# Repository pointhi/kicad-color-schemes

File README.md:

# kicad-color-schemes

Want to change the color scheme of KiCad? Look here for inspiration.

## Install Color Themes using the PCM (KiCad 5.99 demo feature)

If you run KiCad 5.99 which was build including the new Plugin and Content Manager (using the compile option `-DKICAD_PCM=ON`), you can simply add the repository url and install the themes inside KiCad:
- https://raw.githubusercontent.com/pointhi/kicad-color-schemes/master/repository.json

## How to use a colour theme.

Every theme directory contains the colour definition parts of the eeschema and pcbnew setup files found in your personal profile.
- For Linux under ~.config/kicad/
- Windows XP: “C:\Documents and Settings\username\Application Data” + kicad (= %APPDATA%\kicad)
- Windows Vista & later: “C:\Users\username\AppData\Roaming” + kicad (= %APPDATA%\kicad)
- OSX: The user’s home directory + /Library/Preferences/kicad

Use a text editor to overwrite the relevant sections with the data found in the files in this folder. **Make sure you create a backup first.**

The pcbnew config file content has been split into the sections responsible for the footprint editor and the one for pcbnew. This is done to allow you to more easily mix and match different schemes for different tools.

## Automatic patcher

An automatic patch script can be used to transfer a colour scheme into your KiCad settings files. Make sure KiCad is closed before using it.

The script expects the directory containing the colour scheme and the kicad config directory as arguments. Switches are included to disable transfer of a particular part of the scheme definition. (use --help for detailed instructions.) A bakup of your settings files is created before changes are made.

Example:
`python3 patch.py ~/kicad-color-schemes/blue-green-dark/ ~/.config/kicad/`

## JSON themes (for KiCad 6, and "5.99" nightly builds after February 2020)

KiCad 6 is changing to a JSON-based colour theme system.  Recent nightly builds already support the
new system, where each colour theme lives in a JSON file in the `colors` directory of the user
settings path (see "How to use a colour theme" above.)

To use the JSON version of a theme, just copy the file into your `colors` directory.  The next time
you run KiCad, it will detect the new theme file and you will be able to choose it in the
preferences.  Each KiCad application can use a different color theme if you wish.

In the new system, the footprint editor and PcbNew use the same color theme.  If you would like to
have different colours for those two applications, the way to do it is to choose a different theme
file in the PcbNew and footprint editor preferences dialogs.

## eeschema

| color-scheme                                               | screenshot                                                                                                                                  |
| ---------------------------------------------------------- | ------------------------------------------------------------------------------------------------------------------------------------------- |
| **kicad-classic**                                          |  |
| **kicad-2020**                                             |                 |
| **solarized-dark** *http://ethanschoonover.com/solarized*  |           |
| **solarized-light** *http://ethanschoonover.com/solarized* |         |
| **black-white**                                            |                   |
| **blue-tone**                                              |                              |
| **behave-dark** *https://atom.io/themes/behave-theme*      |                 |
| **neon** *Inspired by forum user BobZ*                     |   |
| **nord** *Designed by @0xdec*                              |              |
| **monokai** *Inspired by forum user kickofighto*           |                    |
| **eagle-dark** *Designed by DX-MON, Inspired by EagleCAD*  |                   |
| **wdark** *Designed by wykys, Inspired by One Dark*        |                                                                              |
| **wlight** *Designed by wykys, Inspired by Altium*         |                                                                               |
| **arcana** *Designed by @lethalbit*                       |                       |

## pcbnew
| color-scheme                                              | screenshot                                                                                                                                |
| --------------------------------------------------------- | ----------------------------------------------------------------------------------------------------------------------------------------- |
| **kicad-classic**                                         |  |
| **kicad-2020**                                            |                 |
| **behave-dark** *https://atom.io/themes/behave-theme*     |                 |
| **blue-green-dark**                                       |        |
| **nord** *Designed by @0xdec*                             |              |
| **eagle-dark** *Designed by DX-MON, Inspired by EagleCAD* |         |
| **arcana** *Designed by @lethalbit*                       |                      |

## footprint editor
| color-scheme                                              | screenshot                                                                                                                                          |
| --------------------------------------------------------- | --------------------------------------------------------------------------------------------------------------------------------------------------- |
| **kicad-classic**                                         |  |
| **kicad-2020**                                            |                 |
| **behave-dark** *https://atom.io/themes/behave-theme*     |                 |
| **blue-green-dark**                                       |        |
| **nord** *Designed by @0xdec*                             |              |
| **eagle-dark** *Designed by DX-MON, Inspired by EagleCAD* |         |
| **arcana** *Designed by @lethalbit*                       |                      |

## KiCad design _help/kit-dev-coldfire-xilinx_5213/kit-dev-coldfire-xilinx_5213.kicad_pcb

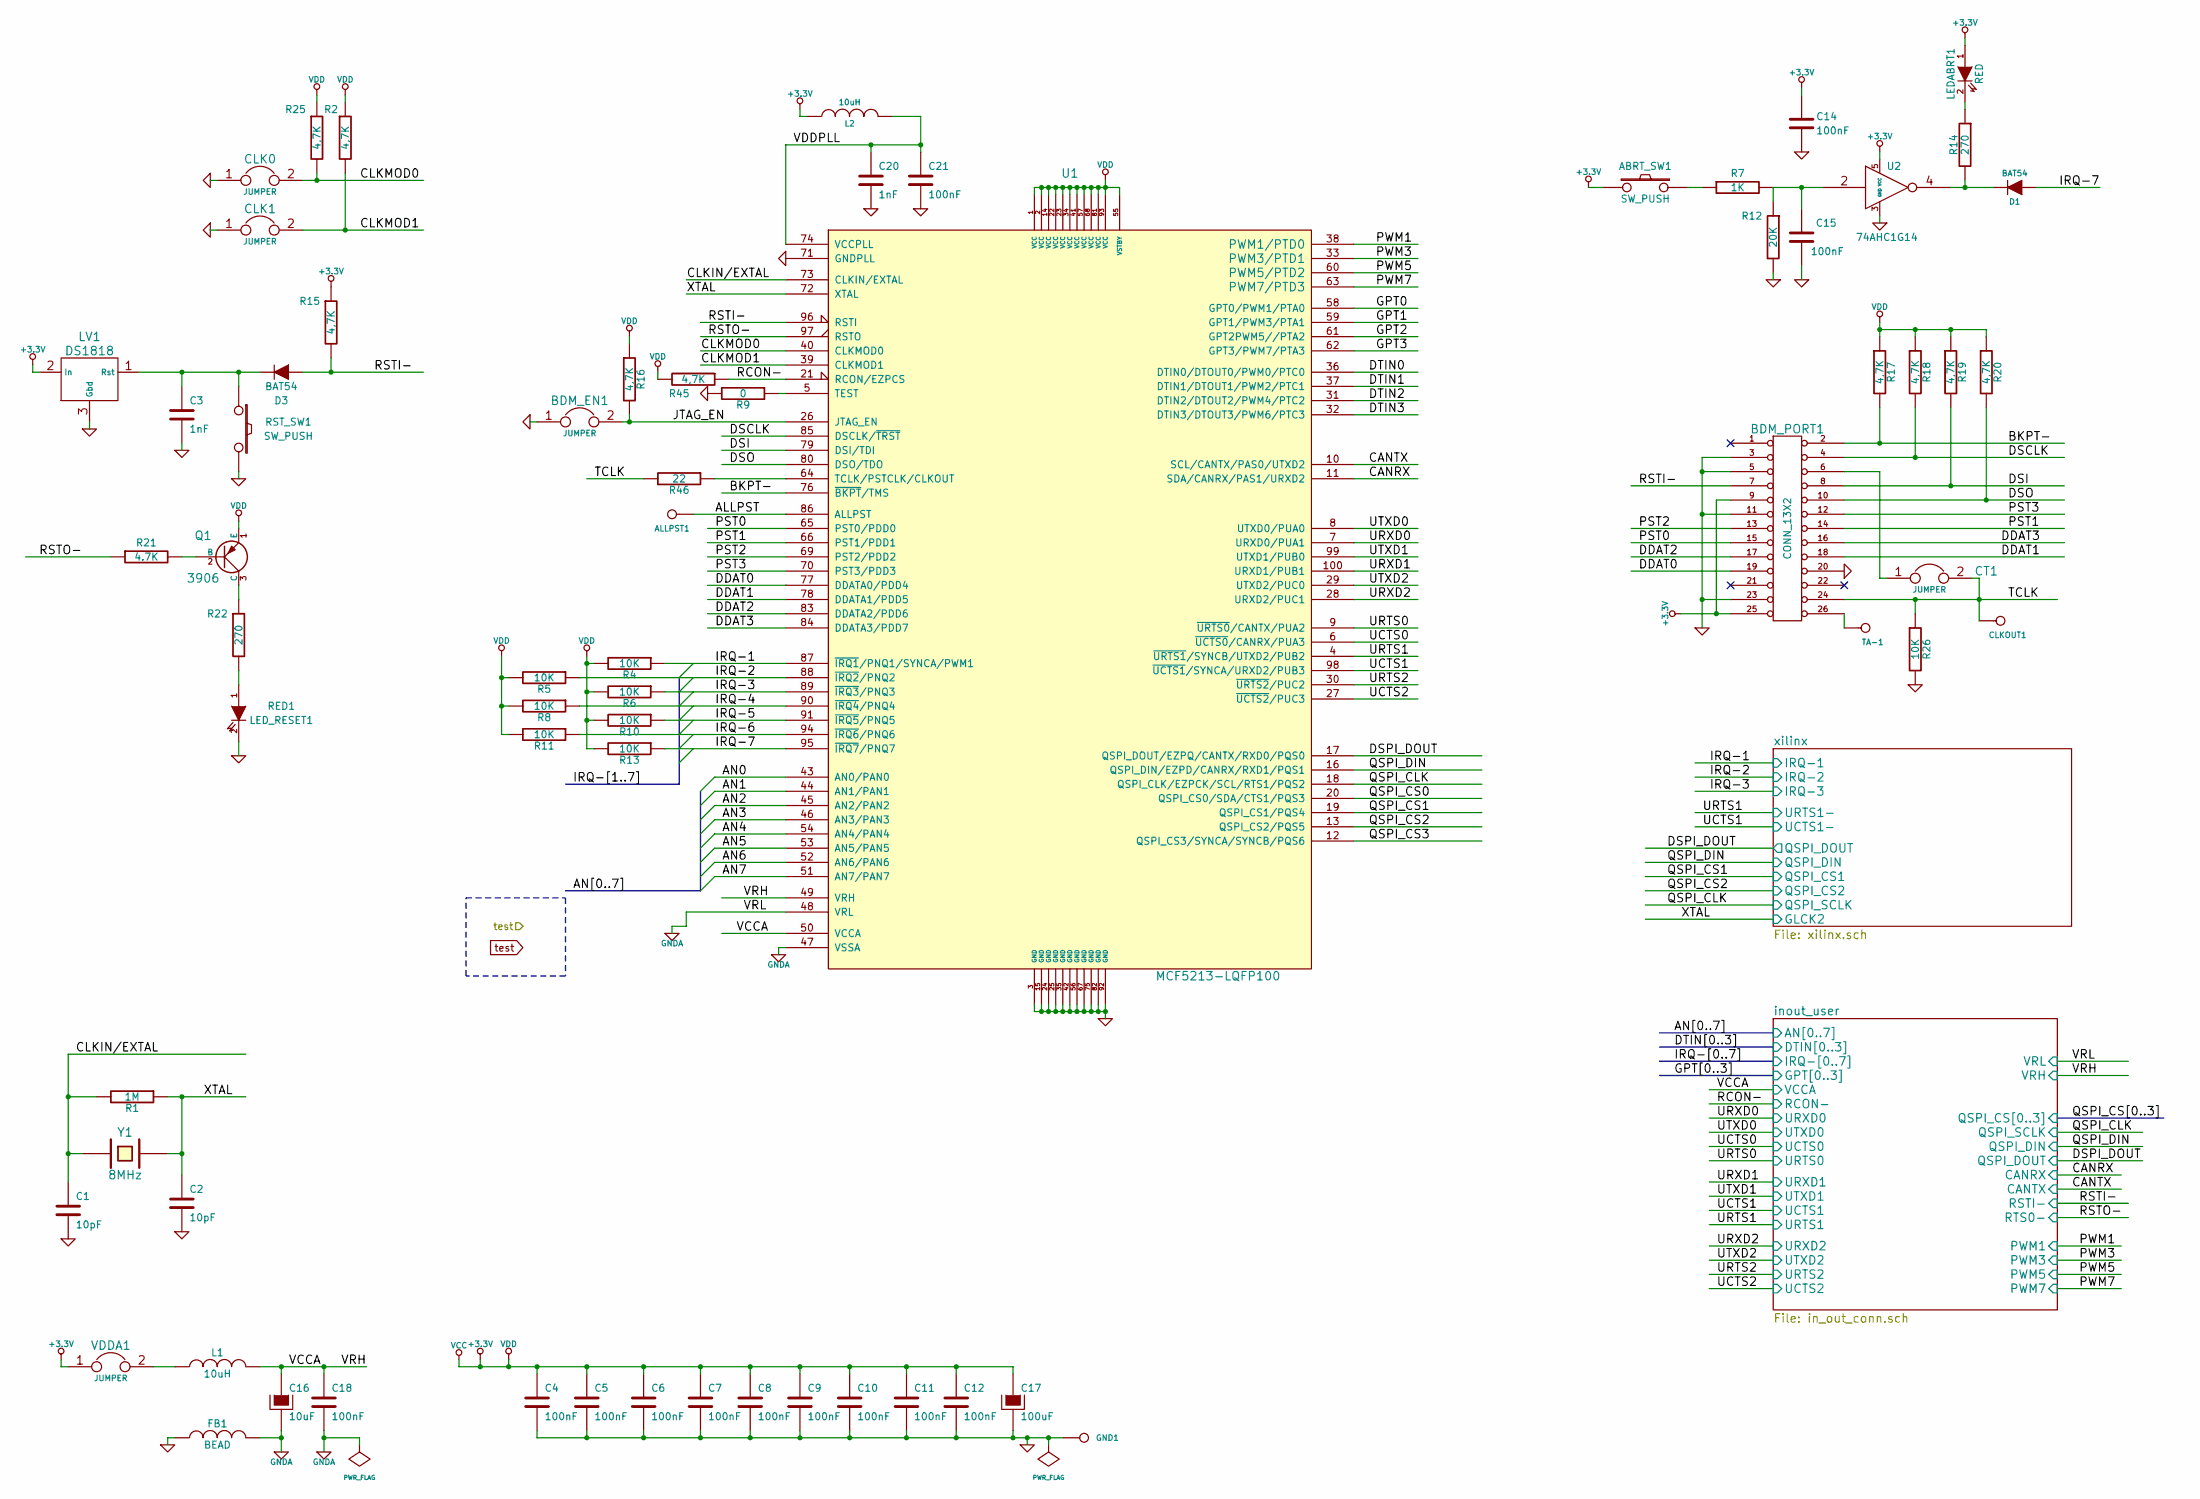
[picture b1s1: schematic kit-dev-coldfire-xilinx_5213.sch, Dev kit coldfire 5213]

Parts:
ABRT_SW1: SW_PUSH; SW_PUSH_SMALL
ALLPST1: CONN_1; PinHeader_1x01_P2.54mm_Vertical
BDM_EN1: JUMPER; PinHeader_1x02_P2.54mm_Vertical
BDM_PORT1: CONN_13X2; PinHeader_2x13_P2.54mm_Vertical
C1, C2: 10pF; R_0805_2012Metric
C3, C20: 1nF; R_0805_2012Metric
C4, C5, C6, C7, C8, C9, C10, C11, C12, C14, C15, C18, C21: 100nF; R_0805_2012Metric
C16: 10uF; SM1206POL
C17: 100uF; SM1206POL
CLK0, CLK1: JUMPER; PinHeader_1x02_P2.54mm_Vertical
CLKOUT1: CONN_1; PinHeader_1x01_P2.54mm_Vertical
CT1: JUMPER; PinHeader_1x02_P2.54mm_Vertical
D1, D3: BAT54; D_SOT-23_ANK
FB1: BEAD; R_1206_3216Metric_Pad1.24x1.80mm_HandSolder
GND1: CONN_1; PinHeader_1x01_P2.54mm_Vertical
L1, L2: 10uH; R_1206_3216Metric_Pad1.24x1.80mm_HandSolder
LEDABRT1: RED; SM1206POL
LV1: DS1818; TO-92_Molded_Narrow
Q1: 3906; SOT23EBC
R1: 1M; R_0805_2012Metric
R2, R15, R16, R17, R18, R19, R20, R25, R45: 4,7K; R_0805_2012Metric
R4, R5, R6, R8, R10, R11, R13, R26: 10K; R_0805_2012Metric
R7: 1K; R_0805_2012Metric
R9: 0; R_0805_2012Metric
R12: 20K; R_0805_2012Metric
R14, R22: 270; R_0805_2012Metric
R21: 4.7K; R_0805_2012Metric
R46: 22; R_0805_2012Metric
RED1: LED_RESET1; SM1206POL
RST_SW1: SW_PUSH; SW_PUSH_SMALL
TA-1: CONN_1; PinHeader_1x01_P2.54mm_Vertical
U1: MCF5213-LQFP100; LQFP-100_14x14mm_P0.5mm
U2: 74AHC1G14; SOT353
VDDA1: JUMPER; PinHeader_1x02_P2.54mm_Vertical
Y1: 8MHz; Crystal_HC18-U_Horizontal

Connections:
+3.3V: ABRT_SW1.2, BDM_PORT1.9, BDM_PORT1.25 (P24), C4.1, C5.1, C6.1, C7.1, C8.1, C9.1, C10.1, C11.1, C12.1, C14.2, C17.1, L2.1, LEDABRT1.1 (A), LV1.2 (In), Q1.1 (E), R2.1, R4.2, R5.2, R6.2, R8.2, R10.2, R11.2, R13.2, R15.1, R16.1, R17.1, R18.1, R19.1, R20.1, R25.1, R45.2, U1.1 (VCC), U1.2 (VCC), U1.14 (VCC), U1.22 (VCC), U1.23 (VCC), U1.34 (VCC), U1.41 (VCC), U1.55 (VSTBY), U1.57 (VCC), U1.68 (VCC), U1.81 (VCC), U1.93 (VCC), U2.5 (VCC), VDDA1.1; also elsewhere on the board
/ALLPST: ALLPST1.1, U1.86 (ALLPST)
/AN0: U1.43 (AN0/PAN0); also elsewhere on the board
/AN1: U1.44 (AN1/PAN1); also elsewhere on the board
/AN2: U1.45 (AN2/PAN2); also elsewhere on the board
/AN3: U1.46 (AN3/PAN3); also elsewhere on the board
/AN4: U1.54 (AN4/PAN4); also elsewhere on the board
/AN5: U1.53 (AN5/PAN5); also elsewhere on the board
/AN6: U1.52 (AN6/PAN6); also elsewhere on the board
/AN7: U1.51 (AN7/PAN7); also elsewhere on the board
/BKPT-: BDM_PORT1.2, R17.2, U1.76 (~BKPT~/TMS)
/CANRX: U1.11 (SDA/CANRX/PAS1/URXD2); also elsewhere on the board
/CANTX: U1.10 (SCL/CANTX/PAS0/UTXD2); also elsewhere on the board
/CLKIN/EXTAL: C1.1, R1.2, U1.73 (CLKIN/EXTAL), Y1.1
/CLKMOD0: CLK0.2, R25.2, U1.40 (CLKMOD0)
/CLKMOD1: CLK1.2, R2.2, U1.39 (CLKMOD1)
/DDAT0: BDM_PORT1.19, U1.77 (DDATA0/PDD4)
/DDAT1: BDM_PORT1.18, U1.78 (DDATA1/PDD5)
/DDAT2: BDM_PORT1.17, U1.83 (DDATA2/PDD6)
/DDAT3: BDM_PORT1.16, U1.84 (DDATA3/PDD7)
/DSCLK: BDM_PORT1.4, R18.2, U1.85 (DSCLK/~TRST~)
/DSI: BDM_PORT1.8, R19.2, U1.79 (DSI/TDI)
/DSO: BDM_PORT1.10, R20.2, U1.80 (DSO/TDO)
/DSPI_DOUT: U1.17 (QSPI_DOUT/EZPQ/CANTX/RXD0/PQS0); also elsewhere on the board
/DTIN0: U1.36 (DTIN0/DTOUT0/PWM0/PTC0); also elsewhere on the board
/DTIN1: U1.37 (DTIN1/DTOUT1/PWM2/PTC1); also elsewhere on the board
/DTIN2: U1.31 (DTIN2/DTOUT2/PWM4/PTC2); also elsewhere on the board
/DTIN3: U1.32 (DTIN3/DTOUT3/PWM6/PTC3); also elsewhere on the board
/GPT0: U1.58 (GPT0/PWM1/PTA0); also elsewhere on the board
/GPT1: U1.59 (GPT1/PWM3/PTA1); also elsewhere on the board
/GPT2: U1.61 (GPT2PWM5//PTA2); also elsewhere on the board
/GPT3: U1.62 (GPT3/PWM7/PTA3); also elsewhere on the board
/IRQ-1: R4.1, U1.87 (~IRQ1~/PNQ1/SYNCA/PWM1); also elsewhere on the board
/IRQ-2: R5.1, U1.88 (~IRQ2~/PNQ2); also elsewhere on the board
/IRQ-3: R6.1, U1.89 (~IRQ3~/PNQ3); also elsewhere on the board
/IRQ-4: R8.1, U1.90 (~IRQ4~/PNQ4); also elsewhere on the board
/IRQ-5: R10.1, U1.91 (~IRQ5~/PNQ5); also elsewhere on the board
/IRQ-6: R11.1, U1.94 (~IRQ6~/PNQ6); also elsewhere on the board
/IRQ-7: D1.2 (A), R13.1, U1.95 (~IRQ7~/PNQ7); also elsewhere on the board
/JTAG_EN: BDM_EN1.2, R16.2, U1.26 (JTAG_EN)
/PST0: BDM_PORT1.15, U1.65 (PST0/PDD0)
/PST1: BDM_PORT1.14, U1.66 (PST1/PDD1)
/PST2: BDM_PORT1.13, U1.69 (PST2/PDD2)
/PST3: BDM_PORT1.12, U1.70 (PST3/PDD3)
/PWM1: U1.38 (PWM1/PTD0); also elsewhere on the board
/PWM3: U1.33 (PWM3/PTD1); also elsewhere on the board
/PWM5: U1.60 (PWM5/PTD2); also elsewhere on the board
/PWM7: U1.63 (PWM7/PTD3); also elsewhere on the board
/QSPI_CLK: U1.18 (QSPI_CLK/EZPCK/SCL/RTS1/PQS2); also elsewhere on the board
/QSPI_CS0: U1.20 (QSPI_CS0/SDA/CTS1/PQS3); also elsewhere on the board
/QSPI_CS1: U1.19 (QSPI_CS1/PQS4); also elsewhere on the board
/QSPI_CS2: U1.13 (QSPI_CS2/PQS5); also elsewhere on the board
/QSPI_CS3: U1.12 (QSPI_CS3/SYNCA/SYNCB/PQS6); also elsewhere on the board
/QSPI_DIN: U1.16 (QSPI_DIN/EZPD/CANRX/RXD1/PQS1); also elsewhere on the board
/RCON-: R45.1, U1.21 (RCON/EZPCS); also elsewhere on the board
/RSTI-: BDM_PORT1.7, D3.2 (A), R15.2, U1.96 (RSTI); also elsewhere on the board
/RSTO-: R21.1, U1.97 (RSTO); also elsewhere on the board
/TCLK: BDM_PORT1.24 (P20), CLKOUT1.1, CT1.2, R26.1, R46.2
/UCTS0: U1.6 (~UCTS0~/CANRX/PUA3); also elsewhere on the board
/UCTS1: U1.98 (~UCTS1~/SYNCA/URXD2/PUB3); also elsewhere on the board
/UCTS2: U1.27 (~UCTS2~/PUC3); also elsewhere on the board
/URTS0: U1.9 (~URTS0~/CANTX/PUA2); also elsewhere on the board
/URTS1: U1.4 (~URTS1~/SYNCB/UTXD2/PUB2); also elsewhere on the board
/URTS2: U1.30 (~URTS2~/PUC2); also elsewhere on the board
/URXD0: U1.7 (URXD0/PUA1); also elsewhere on the board
/URXD1: U1.100 (URXD1/PUB1); also elsewhere on the board
/URXD2: U1.28 (URXD2/PUC1); also elsewhere on the board
/UTXD0: U1.8 (UTXD0/PUA0); also elsewhere on the board
/UTXD1: U1.99 (UTXD1/PUB0); also elsewhere on the board
/UTXD2: U1.29 (UTXD2/PUC0); also elsewhere on the board
/VCCA: C16.1, C18.1, L1.2, U1.49 (VRH), U1.50 (VCCA); also elsewhere on the board
/VDDPLL: C20.1, C21.1, L2.2, U1.74 (VCCPLL)
/XTAL: C2.1, R1.1, U1.72 (XTAL), Y1.2; also elsewhere on the board
GND: BDM_EN1.1, BDM_PORT1.3, BDM_PORT1.5, BDM_PORT1.11, BDM_PORT1.20, BDM_PORT1.23, C1.2, C2.2, C3.2, C4.2, C5.2, C6.2, C7.2, C8.2, C9.2, C10.2, C11.2, C12.2, C14.1, C15.2, C17.2, C20.2, C21.2, CLK0.1, CLK1.1, FB1.1, GND1.1, LV1.3 (Gbd), R9.2, R12.2, R26.2, RED1.2 (K), RST_SW1.2, U1.3 (GND), U1.15 (GND), U1.24 (GND), U1.25 (GND), U1.35 (GND), U1.42 (GND), U1.56 (GND), U1.67 (GND), U1.71 (GNDPLL), U1.75 (GND), U1.82 (GND), U1.92 (GND), U2.3 (GND); also elsewhere on the board
GNDA: C16.2, C18.2, FB1.2, U1.47 (VSSA), U1.48 (VRL); also elsewhere on the board
unnamed: ABRT_SW1.1, R7.1
unnamed: BDM_PORT1.6, CT1.1
unnamed: BDM_PORT1.26 (P22), TA-1.1
unnamed: C3.1, D3.1 (K), LV1.1 (Rst), RST_SW1.1
unnamed: C15.1, R7.2, R12.1, U2.2
unnamed: D1.1 (K), R14.2, U2.4
unnamed: L1.1, VDDA1.2
unnamed: LEDABRT1.2 (K), R14.1
unnamed: Q1.2 (B), R21.2
unnamed: Q1.3 (C), R22.1
unnamed: R9.1, U1.5 (TEST)
unnamed: R22.2, RED1.1 (A)
unnamed: R46.1, U1.64 (TCLK/PSTCLK/CLKOUT)

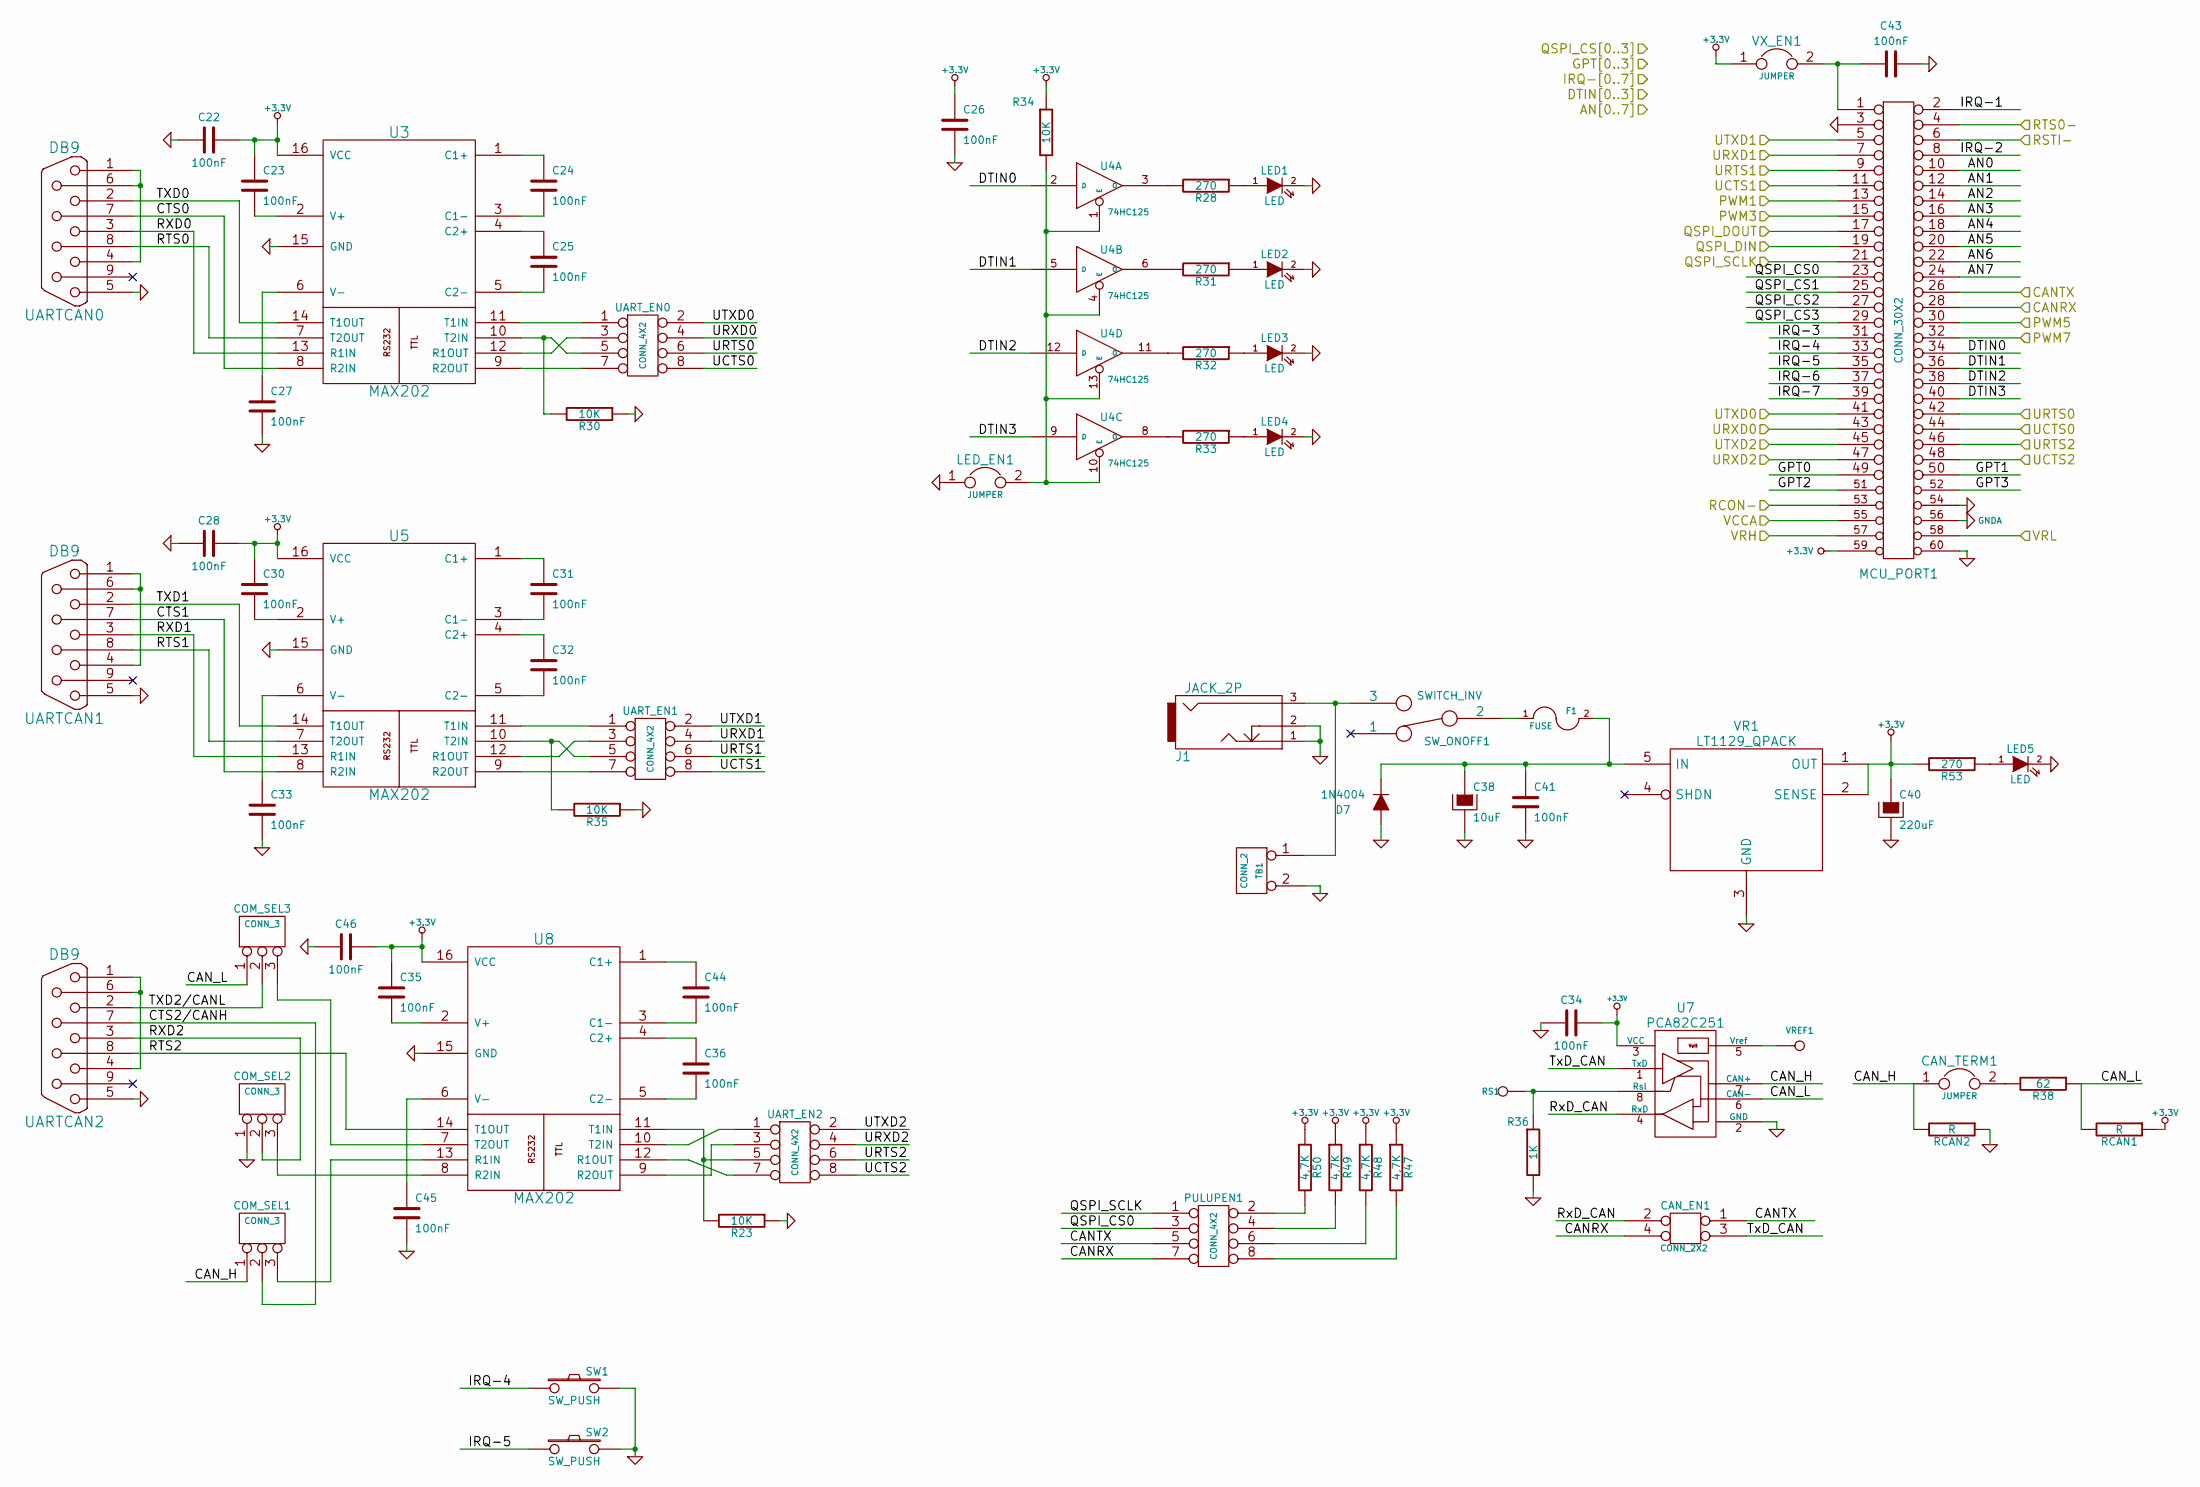
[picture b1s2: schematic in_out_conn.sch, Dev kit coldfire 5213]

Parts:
C22, C23, C24, C25, C26, C27, C28, C30, C31, C32, C33, C34, C35, C36, C41, C43, C44, C45, C46: 100nF; R_0805_2012Metric
C38: 10uF; CP_Radial_D8.0mm_P5.00mm
C40: 220uF; CP_Radial_D8.0mm_P5.00mm
CAN_EN1: CONN_2X2; PinHeader_2x02_P2.54mm_Vertical
CAN_TERM1: JUMPER; PinHeader_1x02_P2.54mm_Vertical
COM_SEL1, COM_SEL2, COM_SEL3: CONN_3; PinHeader_1x03_P2.54mm_Vertical
D7: 1N4004; D_DO-15_P12.70mm_Horizontal
F1: FUSE; FSUPCMS
J1: JACK_2P; JACK_ALIM
LED1, LED2, LED3, LED4, LED5: LED; LED_1206_3216Metric
LED_EN1: JUMPER; PinHeader_1x02_P2.54mm_Vertical
MCU_PORT1: CONN_30X2; PinHeader_2x30_P2.54mm_Vertical
PULUPEN1: CONN_4X2; PinHeader_2x04_P2.54mm_Vertical
R23, R30, R34, R35: 10K; R_0805_2012Metric
R28, R31, R32, R33, R53: 270; R_0805_2012Metric
R36: 1K; R_0805_2012Metric
R38: 62; R_0805_2012Metric
R47, R48, R49, R50: 4,7K; R_0805_2012Metric
RCAN1, RCAN2: R; R_0805_2012Metric
RS1: CONN_1; PinHeader_1x01_P2.54mm_Vertical
SW1, SW2: SW_PUSH; SW_PUSH_SMALL
SW_ONOFF1: SWITCH_INV; SW_SPDT
TB1: CONN_2; bornier2
U3, U5, U8: MAX202; SOIC-16_3.9x9.9mm_P1.27mm
U4: 74HC125; SOIC-14_3.9x8.7mm_P1.27mm
U7: PCA82C251; SOIC-8_3.9x4.9mm_P1.27mm
UARTCAN0, UARTCAN1, UARTCAN2: DB9; DB9FC
UART_EN0, UART_EN1, UART_EN2: CONN_4X2; PinHeader_2x04_P2.54mm_Vertical
VR1: LT1129_QPACK; TO-263-5_TabPin3
VREF1: CONN_1; PinHeader_1x01_P2.54mm_Vertical
VX_EN1: JUMPER; PinHeader_1x02_P2.54mm_Vertical

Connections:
+3.3V: C22.1, C23.1, C26.1, C28.1, C30.1, C34.1, C35.1, C40.1, C46.1, MCU_PORT1.59, R34.1, R47.1, R48.1, R49.1, R50.1, R53.2, RCAN1.1, U3.16 (VCC), U4.14 (VCC), U5.16 (VCC), U7.3 (VCC), U8.16 (VCC), VR1.1 (OUT), VR1.2 (SENSE), VX_EN1.1; also elsewhere on the board
/AN0: MCU_PORT1.10; also elsewhere on the board
/AN1: MCU_PORT1.12; also elsewhere on the board
/AN2: MCU_PORT1.14; also elsewhere on the board
/AN3: MCU_PORT1.16; also elsewhere on the board
/AN4: MCU_PORT1.18; also elsewhere on the board
/AN5: MCU_PORT1.20; also elsewhere on the board
/AN6: MCU_PORT1.22; also elsewhere on the board
/AN7: MCU_PORT1.24; also elsewhere on the board
/CANRX: CAN_EN1.4, MCU_PORT1.28, PULUPEN1.7; also elsewhere on the board
/CANTX: CAN_EN1.1, MCU_PORT1.26, PULUPEN1.5; also elsewhere on the board
/DSPI_DOUT: MCU_PORT1.17; also elsewhere on the board
/DTIN0: MCU_PORT1.34, U4.2 (D); also elsewhere on the board
/DTIN1: MCU_PORT1.36, U4.5 (D); also elsewhere on the board
/DTIN2: MCU_PORT1.38, U4.12 (D); also elsewhere on the board
/DTIN3: MCU_PORT1.40, U4.9 (D); also elsewhere on the board
/GPT0: MCU_PORT1.49; also elsewhere on the board
/GPT1: MCU_PORT1.50; also elsewhere on the board
/GPT2: MCU_PORT1.51; also elsewhere on the board
/GPT3: MCU_PORT1.52; also elsewhere on the board
/IRQ-1: MCU_PORT1.2; also elsewhere on the board
/IRQ-2: MCU_PORT1.8; also elsewhere on the board
/IRQ-3: MCU_PORT1.31; also elsewhere on the board
/IRQ-4: MCU_PORT1.33, SW1.1; also elsewhere on the board
/IRQ-5: MCU_PORT1.35, SW2.1; also elsewhere on the board
/IRQ-6: MCU_PORT1.37; also elsewhere on the board
/IRQ-7: MCU_PORT1.39; also elsewhere on the board
/PWM1: MCU_PORT1.13; also elsewhere on the board
/PWM3: MCU_PORT1.15; also elsewhere on the board
/PWM5: MCU_PORT1.30; also elsewhere on the board
/PWM7: MCU_PORT1.32; also elsewhere on the board
/QSPI_CLK: MCU_PORT1.21, PULUPEN1.1; also elsewhere on the board
/QSPI_CS0: MCU_PORT1.23, PULUPEN1.3; also elsewhere on the board
/QSPI_CS1: MCU_PORT1.25; also elsewhere on the board
/QSPI_CS2: MCU_PORT1.27; also elsewhere on the board
/QSPI_CS3: MCU_PORT1.29; also elsewhere on the board
/QSPI_DIN: MCU_PORT1.19; also elsewhere on the board
/RCON-: MCU_PORT1.53; also elsewhere on the board
/RSTI-: MCU_PORT1.6; also elsewhere on the board
/RSTO-: MCU_PORT1.4; also elsewhere on the board
/UCTS0: MCU_PORT1.44, UART_EN0.8; also elsewhere on the board
/UCTS1: MCU_PORT1.11, UART_EN1.8; also elsewhere on the board
/UCTS2: MCU_PORT1.48, UART_EN2.8; also elsewhere on the board
/URTS0: MCU_PORT1.42, UART_EN0.6; also elsewhere on the board
/URTS1: MCU_PORT1.9, UART_EN1.6; also elsewhere on the board
/URTS2: MCU_PORT1.46, UART_EN2.6; also elsewhere on the board
/URXD0: MCU_PORT1.43, UART_EN0.4; also elsewhere on the board
/URXD1: MCU_PORT1.7, UART_EN1.4; also elsewhere on the board
/URXD2: MCU_PORT1.47, UART_EN2.4; also elsewhere on the board
/UTXD0: MCU_PORT1.41, UART_EN0.2; also elsewhere on the board
/UTXD1: MCU_PORT1.5, UART_EN1.2; also elsewhere on the board
/UTXD2: MCU_PORT1.45, UART_EN2.2; also elsewhere on the board
/VCCA: MCU_PORT1.55, MCU_PORT1.57; also elsewhere on the board
/inout_user/CAN_H: CAN_TERM1.1, COM_SEL1.1, RCAN2.2, U7.7 (CAN+)
/inout_user/CAN_L: COM_SEL3.1, R38.1, RCAN1.2, U7.6 (CAN-)
/inout_user/CTS0: U3.8 (R2IN), UARTCAN0.7
/inout_user/CTS1: U5.8 (R2IN), UARTCAN1.7
/inout_user/CTS2/CANH: COM_SEL1.2 (PM), UARTCAN2.7
/inout_user/RTS0: U3.7 (T2OUT), UARTCAN0.8
/inout_user/RTS1: U5.7 (T2OUT), UARTCAN1.8
/inout_user/RTS2: U8.14 (T1OUT), UARTCAN2.8
/inout_user/RXD0: U3.13 (R1IN), UARTCAN0.3
/inout_user/RXD1: U5.13 (R1IN), UARTCAN1.3
/inout_user/RXD2: COM_SEL2.2 (PM), UARTCAN2.3
/inout_user/RxD_CAN: CAN_EN1.2, U7.4 (RxD)
/inout_user/TXD0: U3.14 (T1OUT), UARTCAN0.2
/inout_user/TXD1: U5.14 (T1OUT), UARTCAN1.2
/inout_user/TXD2/CANL: COM_SEL3.2 (PM), UARTCAN2.2
/inout_user/TxD_CAN: CAN_EN1.3, U7.1 (TxD)
GND: C22.2, C26.2, C27.2, C28.2, C33.2, C34.2, C38.2, C40.2, C41.2, C43.1, C45.2, C46.2, COM_SEL2.1, D7.2 (A), J1.1, J1.2, LED1.2 (K), LED2.2 (K), LED3.2 (K), LED4.2 (K), LED5.2 (K), LED_EN1.1, MCU_PORT1.3, MCU_PORT1.54, MCU_PORT1.60, R23.1, R30.1, R35.1, R36.2, RCAN2.1, SW1.2, SW2.2, TB1.2 (PM), U3.15 (GND), U4.7 (GND), U5.15 (GND), U7.2 (GND), U8.15 (GND), UARTCAN0.5, UARTCAN1.5, UARTCAN2.5, VR1.3 (GND); also elsewhere on the board
GNDA: MCU_PORT1.56, MCU_PORT1.58; also elsewhere on the board
unnamed: C23.2, U3.2 (V+)
unnamed: C24.1, U3.1 (C1+)
unnamed: C24.2, U3.3 (C1-)
unnamed: C25.1, U3.4 (C2+)
unnamed: C25.2, U3.5 (C2-)
unnamed: C27.1, U3.6 (V-)
unnamed: C30.2, U5.2 (V+)
unnamed: C31.1, U5.1 (C1+)
unnamed: C31.2, U5.3 (C1-)
unnamed: C32.1, U5.4 (C2+)
unnamed: C32.2, U5.5 (C2-)
unnamed: C33.1, U5.6 (V-)
unnamed: C35.2, U8.2 (V+)
unnamed: C36.1, U8.4 (C2+)
unnamed: C36.2, U8.5 (C2-)
unnamed: C38.1, C41.1, D7.1 (K), F1.2, VR1.5 (IN)
unnamed: C43.2, MCU_PORT1.1, VX_EN1.2
unnamed: C44.1, U8.1 (C1+)
unnamed: C44.2, U8.3 (C1-)
unnamed: C45.1, U8.6 (V-)
unnamed: CAN_TERM1.2, R38.2
unnamed: COM_SEL1.3, U8.13 (R1IN)
unnamed: COM_SEL2.3, U8.8 (R2IN)
unnamed: COM_SEL3.3, U8.7 (T2OUT)
unnamed: F1.1, SW_ONOFF1.2
unnamed: J1.3, SW_ONOFF1.3, TB1.1
unnamed: LED1.1 (A), R28.1
unnamed: LED2.1 (A), R31.1
unnamed: LED3.1 (A), R32.1
unnamed: LED4.1 (A), R33.1
unnamed: LED5.1 (A), R53.1
unnamed: LED_EN1.2, R34.2, U4.1 (E), U4.4 (E), U4.10 (E), U4.13 (E)
unnamed: PULUPEN1.2, R50.2
unnamed: PULUPEN1.4, R49.2
unnamed: PULUPEN1.6, R48.2
unnamed: PULUPEN1.8, R47.2
unnamed: R23.2, U8.11 (T1IN), UART_EN2.5
unnamed: R28.2, U4.3 (O)
unnamed: R30.2, U3.10 (T2IN), UART_EN0.5
unnamed: R31.2, U4.6 (O)
unnamed: R32.2, U4.11 (O)
unnamed: R33.2, U4.8 (O)
unnamed: R35.2, U5.10 (T2IN), UART_EN1.5
unnamed: R36.1, RS1.1, U7.8 (Rsl)
unnamed: U3.9 (R2OUT), UART_EN0.7
unnamed: U3.11 (T1IN), UART_EN0.1
unnamed: U3.12 (R1OUT), UART_EN0.3
unnamed: U5.9 (R2OUT), UART_EN1.7
unnamed: U5.11 (T1IN), UART_EN1.1
unnamed: U5.12 (R1OUT), UART_EN1.3
unnamed: U7.5 (Vref), VREF1.1
unnamed: U8.9 (R2OUT), UART_EN2.3
unnamed: U8.10 (T2IN), UART_EN2.1
unnamed: U8.12 (R1OUT), UART_EN2.7
unnamed: UARTCAN0.1, UARTCAN0.4, UARTCAN0.6
unnamed: UARTCAN1.1, UARTCAN1.4, UARTCAN1.6
unnamed: UARTCAN2.1, UARTCAN2.4, UARTCAN2.6

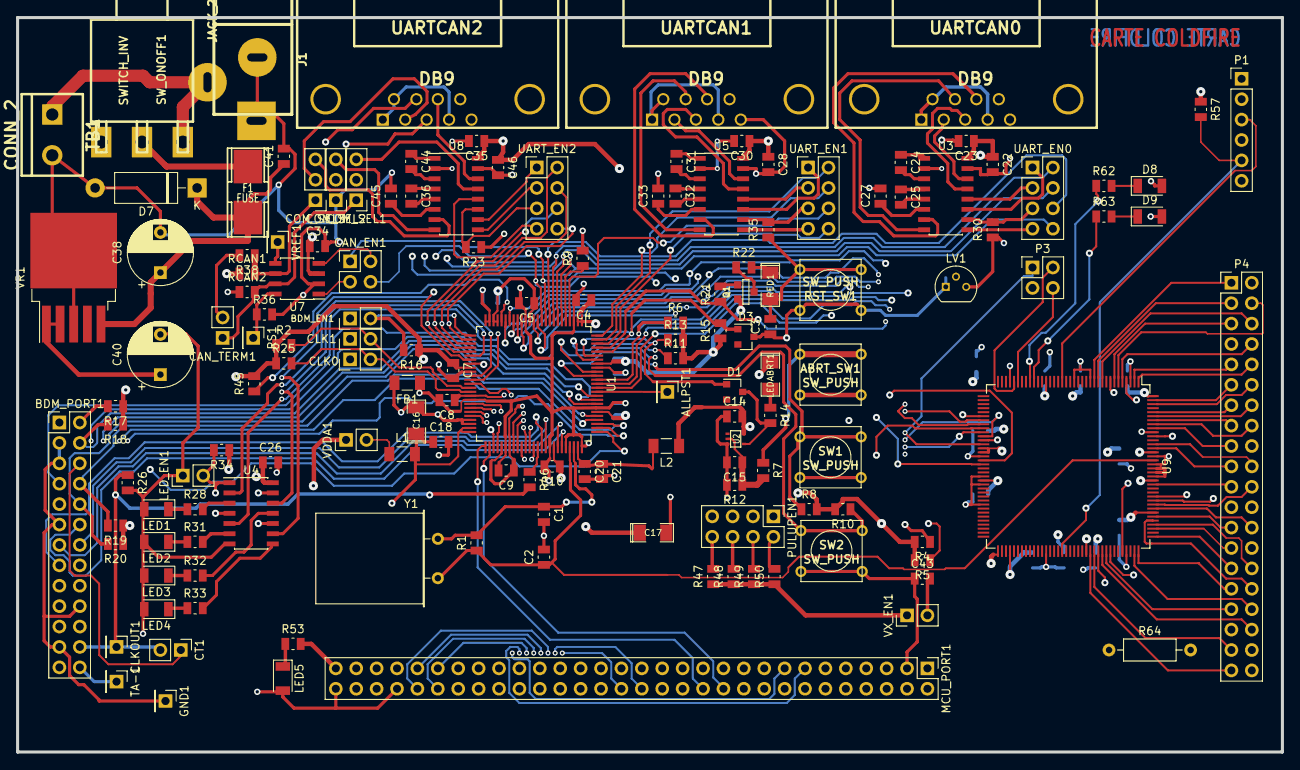
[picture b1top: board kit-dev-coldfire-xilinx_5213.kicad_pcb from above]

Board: 4 copper layers, 157.5 x 91.4 mm, 162 parts (0 on the bottom side), 209 nets.

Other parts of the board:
C51, C52, C53, C54, C55, C56, C57, C58, C59, C60, C61: 100nF; R_0805_2012Metric
D8, D9: LED; LED_1206_3216Metric
P1: CONN_6; PinHeader_1x06_P2.54mm_Vertical
P3: CONN_2X2; PinHeader_2x02_P2.54mm_Vertical
P4: CONN_20X2; PinHeader_2x20_P2.54mm_Vertical
R57: 4K7; R_0805_2012Metric
R62, R63: 1K; R_0805_2012Metric
R64: 3,3; R_Axial_DIN0207_L6.3mm_D2.5mm_P10.16mm_Horizontal
U9: XCR3256-TQ144; TQFP-144_20x20mm_P0.5mm

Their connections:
+3.3V: C51.1, C52.1, C53.1, C54.1, C55.1, C56.1, C57.1, C58.1, C59.1, C60.1, C61.1, P1.1, R57.1, R64.1, U9.24, U9.50, U9.51, U9.58, U9.73, U9.76, U9.95, U9.115, U9.123, U9.130, U9.144; also elsewhere on the board
/DSPI_DOUT: U9.47; also elsewhere on the board
/IRQ-1: U9.42; also elsewhere on the board
/IRQ-2: U9.43; also elsewhere on the board
/IRQ-3: U9.44; also elsewhere on the board
/QSPI_CLK: U9.48; also elsewhere on the board
/QSPI_CS1: U9.54; also elsewhere on the board
/QSPI_CS2: U9.45; also elsewhere on the board
/QSPI_DIN: U9.46; also elsewhere on the board
/UCTS1: P3.1, U9.49; also elsewhere on the board
/URTS1: P3.3, U9.53; also elsewhere on the board
/XTAL: U9.128; also elsewhere on the board
/xilinx/+3,3V_OUT: P4.38, R64.2
/xilinx/LED_TEST1: R62.1, U9.28
/xilinx/LED_TEST2: R63.1, U9.27
/xilinx/TCK: P1.5, R57.2, U9.89
/xilinx/TDI: P1.4, U9.4
/xilinx/TDO: P1.6, U9.104
/xilinx/TMS: P1.3, U9.20
/xilinx/XIL_D0: P4.1, U9.12
/xilinx/XIL_D1: P4.3, U9.11
/xilinx/XIL_D2: P4.5, U9.7
/xilinx/XIL_D3: P4.7, U9.8
/xilinx/XIL_D4: P4.9, U9.2
/xilinx/XIL_D5: P4.11, U9.143
/xilinx/XIL_D6: P4.13, U9.140
/xilinx/XIL_D7: P4.15, U9.138
/xilinx/XIL_D8: P4.17, U9.136
/xilinx/XIL_D9: P4.19, U9.131
/xilinx/XIL_D10: P4.21, U9.122
/xilinx/XIL_D11: P4.23, U9.119
/xilinx/XIL_D12: P4.25, U9.114
/xilinx/XIL_D13: P4.27, U9.111
/xilinx/XIL_D14: P4.29, U9.109
/xilinx/XIL_D15: P4.31, U9.108
/xilinx/XIL_D16: P4.33, U9.100
/xilinx/XIL_D17: P4.35, U9.101
/xilinx/XIL_D18: P4.37, U9.97
/xilinx/XIL_D19: P4.39, U9.96
/xilinx/XIL_D20: P4.4, U9.6
/xilinx/XIL_D21: P4.6, U9.10
/xilinx/XIL_D22: P4.8, U9.5
/xilinx/XIL_D23: P4.10, U9.1
/xilinx/XIL_D24: P4.12, U9.142
/xilinx/XIL_D25: P4.14, U9.139
/xilinx/XIL_D26: P4.16, U9.137
/xilinx/XIL_D27: P4.18, U9.134
/xilinx/XIL_D28: P4.20, U9.132
/xilinx/XIL_D29: P4.22, U9.117
/xilinx/XIL_D30: P4.24, U9.118
/xilinx/XIL_D31: P4.26, U9.116
/xilinx/XIL_D32: P4.28, U9.98
/xilinx/XIL_D33: P4.30, U9.112
/xilinx/XIL_D34: P4.32, U9.113
/xilinx/XIL_D35: P4.34, U9.107
/xilinx/XIL_D36: P4.36, U9.99
GND: C51.2, C52.2, C53.2, C54.2, C55.2, C56.2, C57.2, C58.2, C59.2, C60.2, C61.2, D8.2, D9.2, P1.2, P4.2, P4.40, U9.3, U9.13, U9.17, U9.33, U9.52, U9.57, U9.59, U9.64, U9.85, U9.105, U9.124, U9.125, U9.126, U9.127, U9.129, U9.135; also elsewhere on the board
unnamed: D8.1, R62.2
unnamed: D9.1, R63.2
unnamed: P3.2, U9.32
unnamed: P3.4, U9.31

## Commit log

2018-06-30 Some initial color schemes
2018-06-30 Add basic README
2018-06-30 Add demo project, fix solarized-light screenshot
2018-06-30 Create LICENSE
2018-06-30 Add little readme
2019-05-01 add installation description and modedit, pcbnew sections to README
2019-05-01 Add default kicad themes for footprint editor and pcbnew
2019-05-01 Add behave theme for eeschema, footprint editor and pcbnew
2019-05-01 add behave theme to readme
2019-05-01 Updated example
    - prepared pcb side for screenshots
    - added ERC error source and subsheet to schematic screenshot area.
2019-05-05 Add blue-tone theme
2019-05-05 update eeschema default screenshot
2019-05-05 update blue tone image (forgot to save after cropping)
2019-05-05 Add layer colours missed in behave theme (the ones with transparency)
2019-05-05 Dark blue/green pcbnew colour theme based on light blue tone eeschema theme
2019-05-05 fix table formatting
2019-05-07 added patcher
2019-05-07 fixed: made it less fuzzy
2019-07-28 More powerful patch script
2019-07-28 Create a bakup of the settingsfiles before doing anything
2019-07-28 Correct shebang line
2019-11-26 fixing issue #8, plus minor fp editor patch issue
    fixing https://github.com/pointhi/kicad-color-schemes/issues/8
2019-11-27 improved 'patch.py' compatibility
2020-01-03 Add neon coloured EESchema theme by forum user BobZ
2020-01-03 [FIX] Add missing definitions
    Some themes did not define some of the eeschema colours. Examples
    are the cursor and wroksheet colour as well as the new spelling
    for the highlight colour
2020-01-04 [ENH] Make highlighting possible in black/white scheme
2020-01-04 [ENH] Update screenshots (unify all of them)
2020-02-24 Add migration script to generate V6 theme files
2020-02-24 Add documentation for new theme system
2020-02-24 Add migrated versions of files
2020-02-25 Add monokai theme as suggested in issue #14
    Originally designed by forum user kickofighto
    https://forum.kicad.info/t/monokai-clone-theme-for-eeschema/12917
2020-05-11 Remove typo line
2020-05-31 Update patcher to automatically pull default config path
2020-05-31 Add script to migrate v6-style configs
2020-07-19 New theme based on nord colors.
    This theme was extracted from @0xdec dot files found here: https://gitlab.com/0xdec/dotfiles/-/tree/master/kicad/.config/kicad
    His theme is based on the nordtheme found here: https://www.nordtheme.com/
2020-07-20 nord: Added screenshots and README entries.
2020-09-21 Done a first pass at adding my version of the Eagle colour scheme based on what I have configured so far
2020-09-21 Cleaned up the schematic eagle colour scheme a bit for contrast and item distinction
2020-09-21 Improved the colouring of adhesion and paste layers for pcbnew and the part editor
2020-09-21 Fixed a couple of mistakes made saying 'rgb' where I meant 'rgba'
2020-09-21 Cleaned up and fixed a couple more colours in the footprint and PCB editors
2020-09-22 Moved the footprint editor colour settings out into their own file so the patcher is happy
2020-10-10 Added a screenshot for the schematic view for the README
2020-10-10 Added support for 8-layer boards to the Eagle theme
2020-10-10 Added screenshots of the footprint and PCB editors for the Eagle theme
2020-10-10 Added entries to the README for the Eagle theme
2020-10-10 Created a KiCAD v6 compatible version of the eagle theme
2020-10-18 Add KiCad 2020 color theme
    Also rename kicad-default to kicad-classic for clarity
2020-11-27 Reorganized structure to minimize top-level folders
2020-11-27 Added themes from kicad-colors repository
2020-11-27 Added Makefile and theme selection script
2020-11-27 Added .gitignore for virtual environment and backup folders
2020-11-27 Removed virtual environment from make flow, no extra Python packages are currently needed
2020-11-27 Fixed bugs for Windows OS
2020-11-28 Changed backups to be stored and sourced from preferences directory
2020-11-28 Updated README, added new theme images
2020-11-28 Added backup section to readme, fixed a broken link
2020-11-28 Trying only relative paths for images
2021-04-12 Created wlight theme
2021-07-04 Update Nord version to prevent JSON parse error
    Recent KiCad nightlies (Version: (5.99.0-11076-g4c8a4e3d47), release build) do not seem to play nicely with a version number of 0 for color themes. With a version number of 0, KiCad crashes with a `j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
2021-10-30 Initial try to create our own PCM repository
2021-10-30 Add first theme package (solarized-dark)
2021-10-30 Improve color theme to be actually installable
2021-10-30 Add ability to add icon into package
2021-10-30 Add metadata.json to themes created by me
2021-10-30 Fix sw theme and rename to black-white
2021-10-30 Improve black/white theme
2021-10-30 Improve readme
2021-10-30 Create icons and add them to the package
2021-10-30 Add ressurce file
2021-10-30 Correct resources
2021-10-30 Add eagle package
2021-10-30 Add wlight theme (and missing eagle package)
2021-10-30 Add code for pcb icon generation
2021-10-31 Improve solarized color-schemes by adding missing colors and improving the description
2021-10-31 Remove sheet background from solarized theme again
2021-10-31 Update black-white theme
2021-11-06 Update to new schema url and idientifier naming
2021-11-13 Initial package of nord theme
    I had to update the json and guess some colors
2021-11-13 Make new version of schematic only themes, to add this information into the color-theme name
2021-11-13 Eagle -> Eagle Dark including package and new icon
2021-11-13 Fixup nord author
2021-11-13 Update wlight theme (schematic only), remove not required color-definitions
2021-11-13 Update repository
2021-12-04 Created wDark theme
2021-12-05 Fix version of color-scheme files
2021-12-31 Added Arcana color theme
2022-04-08 Build json file for neon theme
    Required for KiCad v6.0
